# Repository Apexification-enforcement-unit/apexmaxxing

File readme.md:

# Eye of Ra apex team

## This repo currently contains:
- [game backend](game-backend/)
- [game frontend](game-frontend/)
- [rust sensors](rust_sensors/)
- [DS18B20 to Raspberry](DS18B20_to_Raspberry/)

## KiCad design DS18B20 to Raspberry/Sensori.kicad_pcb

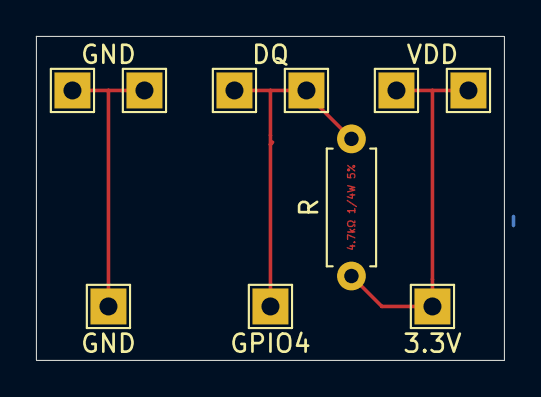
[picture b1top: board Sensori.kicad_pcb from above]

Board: 2 copper layers, 26.0 x 18.0 mm, 10 parts (0 on the bottom side), 3 nets.

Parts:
R: 4.7kΩ 1/4W 5%; R_Axial_DIN0207_L6.3mm_D2.5mm_P7.62mm_Horizontal
TP1, TP7: GND; TestPoint_THTPad_2.0x2.0mm_Drill1.0mm
TP2: GND DS18B20 (Black); TestPoint_THTPad_2.0x2.0mm_Drill1.0mm
TP3: DQ DS18B20 (Yellow); TestPoint_THTPad_2.0x2.0mm_Drill1.0mm
TP4: DQ; TestPoint_THTPad_2.0x2.0mm_Drill1.0mm
TP5: VDD DS18B20 (Red); TestPoint_THTPad_2.0x2.0mm_Drill1.0mm
TP6: VDD; TestPoint_THTPad_2.0x2.0mm_Drill1.0mm
TP8: GPIO4; TestPoint_THTPad_2.0x2.0mm_Drill1.0mm
TP9: 3.3V; TestPoint_THTPad_2.0x2.0mm_Drill1.0mm

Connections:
unnamed: R.1, TP5.1, TP6.1, TP9.1
unnamed: R.2, TP3.1, TP4.1, TP8.1
unnamed: TP1.1, TP2.1, TP7.1

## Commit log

2025-04-29 batman
2025-04-29 add justfile
2025-05-03 implemented chats and fixed some stuff.
2025-05-09 Create s
2025-05-11 did some image tomfoolery
